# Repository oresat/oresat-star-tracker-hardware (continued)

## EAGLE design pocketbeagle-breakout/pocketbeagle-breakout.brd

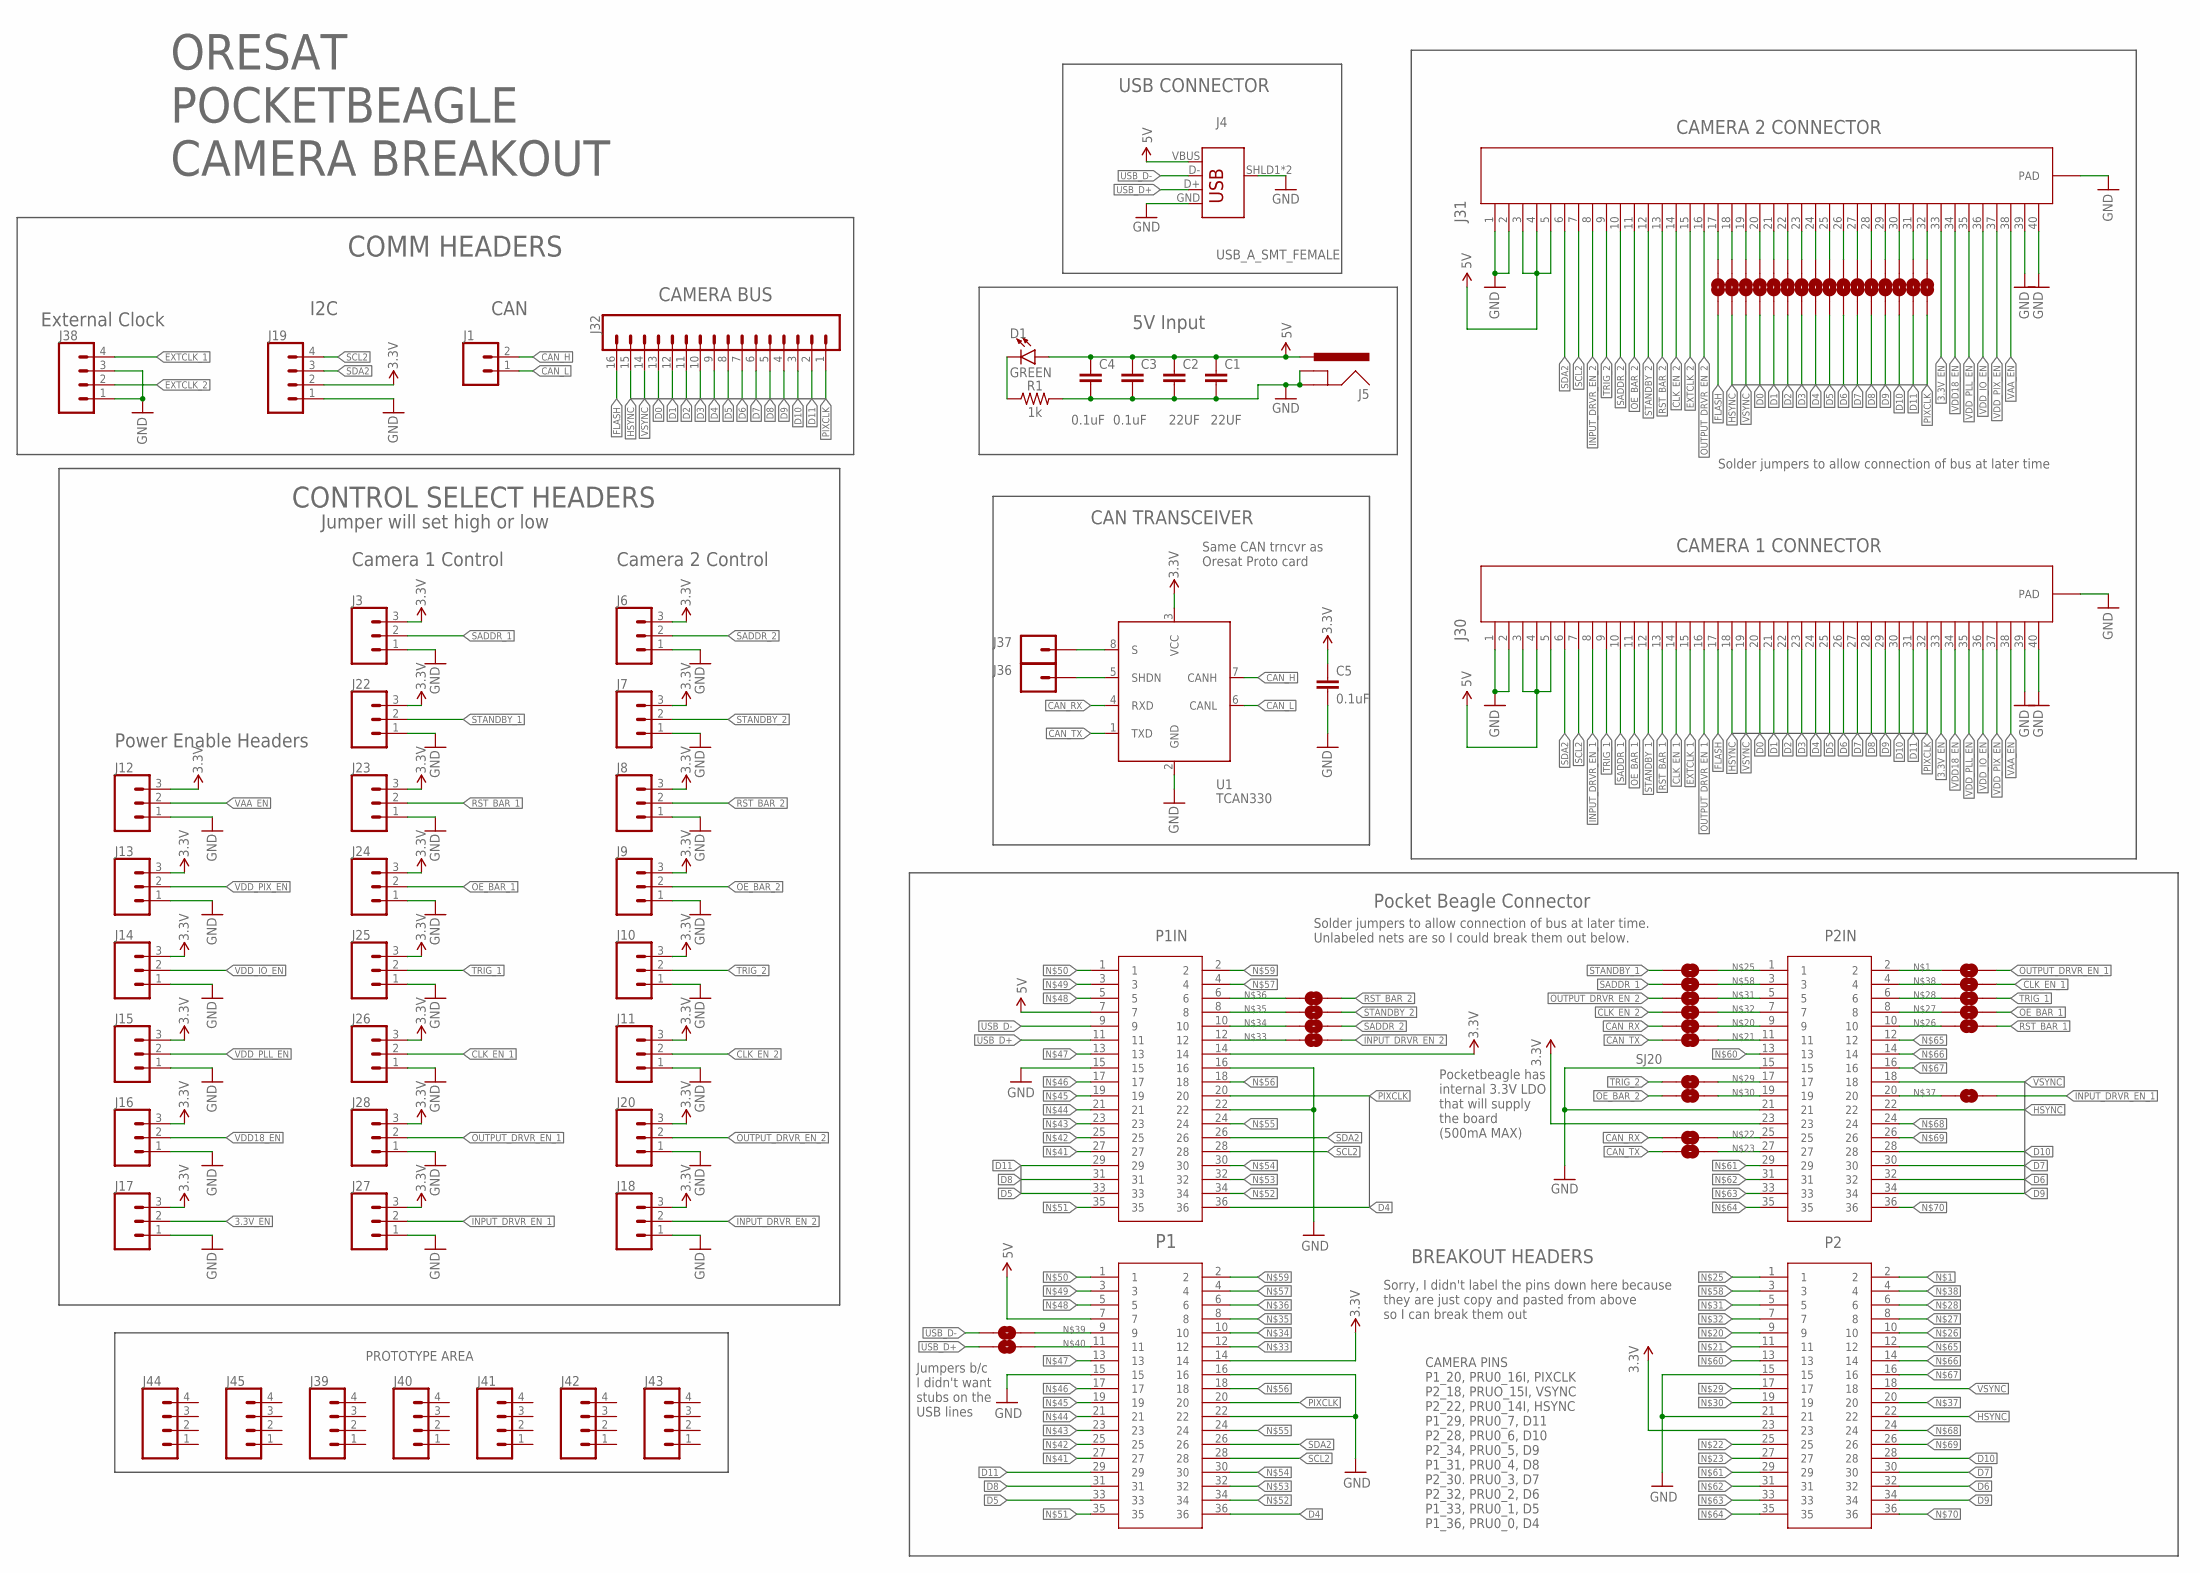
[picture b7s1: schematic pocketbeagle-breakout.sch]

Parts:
C1, C2: 22UF; 1210
C3, C4, C5: 0.1uF; 0603
D1: GREEN; LED-0603
J1: CONN_025MM; SCREWTERMINAL-5MM-2
J3, J6, J7, J8, J9, J10, J11, J12, J13, J14, J15, J16, J17, J18, J20, J22, J23, J24, J25, J26, J27, J28: CONN_031X03_NO_SILK; 1X03_NO_SILK
J4: USB_A_SMT_FEMALE; USB-A-S-SILK-FEMALE
J5: POWER_JACK; POWER_JACK_PTH
J19, J38, J39, J40, J41, J42, J43, J44, J45: CONN_041X04_NO_SILK; 1X04_NO_SILK
J30, J31: 4-1734592-04-1734592-0; TE_4-1734592-0
J32: CONN_161X16_NO_SILK; 1X16_NO_SILK
J36, J37: CONN_01PTH_NO_SILK_YES_STOP; 1X01_NO_SILK
P1, P1IN, P2, P2IN: BCS-118-L-D-TE; CON36_2X18_TU_BCS
R1: 1k; 0603
SJ1, SJ2, SJ3, SJ4, SJ5, SJ6, SJ7, SJ8, SJ9, SJ10, SJ11, SJ12, SJ13, SJ14, SJ15, SJ16: SOLDERJUMPERNC2; SJ_2S-NOTRACE
SJ17, SJ18, SJ21, SJ22, SJ23, SJ24, SJ25, SJ26, SJ27, SJ28, SJ29, SJ30, SJ31, SJ32, SJ33, SJ34, SJ35, SJ36, SJ37, SJ38: SOLDERJUMPERNC; SJ_2S
SJ19, SJ20: SOLDERJUMPERTRACE; SJ_2S-TRACE
U1: TCAN330; SOT23-8_TI-DCN

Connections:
3.3V: C5.1, J3.3, J6.3, J7.3, J8.3, J9.3, J10.3, J11.3, J12.3, J13.3, J14.3, J15.3, J16.3, J17.3, J18.3, J19.2, J20.3, J22.3, J23.3, J24.3, J25.3, J26.3, J27.3, J28.3, P1.14, P1IN.14, P2.23, P2IN.23, U1.3 (VCC)
3.3V_EN: J17.2, J30.33, J31.33
5V: C1.1, C2.1, C3.1, C4.1, D1.A, J4.VBUS, J5.PWR, J30.3, J30.4, J30.5, J31.3, J31.4, J31.5, P1.7, P1IN.7
CAN_H: J1.2, U1.7 (CANH)
CAN_L: J1.1, U1.6 (CANL)
CAN_RX: SJ17.2, SJ19.2, U1.4 (RXD)
CAN_TX: SJ18.2, SJ20.2, U1.1 (TXD)
CLK_EN_1: J26.2, J30.14, SJ36.1
CLK_EN_2: J11.2, J31.14, SJ29.2
D0: J30.20, J32.13, SJ15.1
D1: J30.21, J32.12, SJ14.1
D2: J30.22, J32.11, SJ13.1
D3: J30.23, J32.10, SJ12.1
D4: J30.24, J32.9, P1.36, P1IN.36, SJ11.1
D5: J30.25, J32.8, P1.33, P1IN.33, SJ10.1
D6: J30.26, J32.7, P2.32, P2IN.32, SJ9.1
D7: J30.27, J32.6, P2.30, P2IN.30, SJ8.1
D8: J30.28, J32.5, P1.31, P1IN.31, SJ7.1
D9: J30.29, J32.4, P2.34, P2IN.34, SJ6.1
D10: J30.30, J32.3, P2.28, P2IN.28, SJ5.1
D11: J30.31, J32.2, P1.29, P1IN.29, SJ4.1
EXTCLK_1: J30.15, J38.4
EXTCLK_2: J31.15, J38.2
FLASH: J30.17, J32.16, SJ16.2
GND: C1.2, C2.2, C3.2, C4.2, C5.2, J3.1, J4.GND, J4.SHLD1 (SHIELD), J4.SHLD2 (SHIELD), J5.GND, J5.GNDBREAK, J6.1, J7.1, J8.1, J9.1, J10.1, J11.1, J12.1, J13.1, J14.1, J15.1, J16.1, J17.1, J18.1, J19.1, J20.1, J22.1, J23.1, J24.1, J25.1, J26.1, J27.1, J28.1, J30.1, J30.2, J30.39, J30.40, J30.S1 (PAD), J30.S2 (PAD), J31.1, J31.2, J31.39, J31.40, J31.S1 (PAD), J31.S2 (PAD), J38.1, J38.3, P1.15, P1.16, P1.22, P1IN.15, P1IN.16, P1IN.22, P2.15, P2.21, P2IN.15, P2IN.21, R1.2, U1.2 (GND)
HSYNC: J30.18, J32.15, P2.22, P2IN.22, SJ3.1
INPUT_DRVR_EN_1: J27.2, J30.8, SJ35.2
INPUT_DRVR_EN_2: J18.2, J31.8, SJ33.1
unnamed: P2.2, P2IN.2, SJ34.1
unnamed: J31.17, SJ16.1
unnamed: J31.18, SJ3.2
unnamed: J31.19, SJ2.2
unnamed: J31.20, SJ15.2
unnamed: J31.21, SJ14.2
unnamed: J31.22, SJ13.2
unnamed: J31.23, SJ12.2
unnamed: J31.24, SJ11.2
unnamed: J31.25, SJ10.2
unnamed: J31.26, SJ9.2
unnamed: J31.27, SJ8.2
unnamed: J31.28, SJ7.2
unnamed: J31.29, SJ6.2
unnamed: J31.30, SJ5.2
unnamed: J31.31, SJ4.2
unnamed: J31.32, SJ1.2
unnamed: J36.1, U1.5 (SHDN)
unnamed: J37.1, U1.8 (S)
unnamed: P2.9, P2IN.9, SJ19.1
unnamed: P2.11, P2IN.11, SJ20.1
unnamed: P2.25, P2IN.25, SJ17.1
unnamed: P2.27, P2IN.27, SJ18.1
unnamed: D1.C, R1.1
unnamed: P2.1, P2IN.1, SJ22.2
unnamed: P2.10, P2IN.10, SJ23.2
unnamed: P2.8, P2IN.8, SJ24.2
unnamed: P2.6, P2IN.6, SJ25.2
unnamed: P2.17, P2IN.17, SJ26.1
unnamed: P2.19, P2IN.19, SJ27.1
unnamed: P2.5, P2IN.5, SJ28.1
unnamed: P2.7, P2IN.7, SJ29.1
unnamed: P1.12, P1IN.12, SJ33.2
unnamed: P1.10, P1IN.10, SJ32.2
unnamed: P1.8, P1IN.8, SJ31.2
unnamed: P1.6, P1IN.6, SJ30.2
unnamed: P2.20, P2IN.20, SJ35.1
unnamed: P2.4, P2IN.4, SJ36.2
unnamed: P1.9, SJ37.1
unnamed: P1.11, SJ38.1
unnamed: P1.27, P1IN.27
unnamed: P1.25, P1IN.25
unnamed: P1.23, P1IN.23
unnamed: P1.21, P1IN.21
unnamed: P1.19, P1IN.19
unnamed: P1.17, P1IN.17
unnamed: P1.13, P1IN.13
unnamed: P1.5, P1IN.5
unnamed: P1.3, P1IN.3
unnamed: P1.1, P1IN.1
unnamed: P1.35, P1IN.35
unnamed: P1.34, P1IN.34
unnamed: P1.32, P1IN.32
unnamed: P1.30, P1IN.30
unnamed: P1.24, P1IN.24
unnamed: P1.18, P1IN.18
unnamed: P1.4, P1IN.4
unnamed: P2.3, P2IN.3, SJ21.2
unnamed: P1.2, P1IN.2
unnamed: P2.13, P2IN.13
unnamed: P2.29, P2IN.29
unnamed: P2.31, P2IN.31
unnamed: P2.33, P2IN.33
unnamed: P2.35, P2IN.35
unnamed: P2.12, P2IN.12
unnamed: P2.14, P2IN.14
unnamed: P2.16, P2IN.16
unnamed: P2.24, P2IN.24
unnamed: P2.26, P2IN.26
unnamed: P2.36, P2IN.36
OE_BAR_1: J24.2, J30.11, SJ24.1
OE_BAR_2: J9.2, J31.11, SJ27.2
OUTPUT_DRVR_EN_1: J28.2, J30.16, SJ34.2
OUTPUT_DRVR_EN_2: J20.2, J31.16, SJ28.2
PIXCLK: J30.32, J32.1, P1.20, P1IN.20, SJ1.1
RST_BAR_1: J23.2, J30.13, SJ23.1
RST_BAR_2: J8.2, J31.13, SJ30.1
SADDR_1: J3.2, J30.10, SJ21.1
SADDR_2: J6.2, J31.10, SJ32.1
SCL2: J19.4, J30.7, J31.7, P1.28, P1IN.28
SDA2: J19.3, J30.6, J31.6, P1.26, P1IN.26
STANDBY_1: J22.2, J30.12, SJ22.1
STANDBY_2: J7.2, J31.12, SJ31.1
TRIG_1: J25.2, J30.9, SJ25.1
TRIG_2: J10.2, J31.9, SJ26.2
USB_D+: J4.D+, P1IN.11, SJ38.2
USB_D-: J4.D-, P1IN.9, SJ37.2
VAA_EN: J12.2, J30.38, J31.38
VDD18_EN: J16.2, J30.34, J31.34
VDD_IO_EN: J14.2, J30.36, J31.36
VDD_PIX_EN: J13.2, J30.37, J31.37
VDD_PLL_EN: J15.2, J30.35, J31.35
VSYNC: J30.19, J32.14, P2.18, P2IN.18, SJ2.1

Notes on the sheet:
I2C
Camera 2 Control
CAMERA PINS P1_20, PRU0_16I, PIXCLK P2_18, PRUO_15I, VSYNC P2_22, PRU0_14I, HSYNC P1_29, PRU0_7, D11 P2_28, PRU0_6, D10 P2_34, PRU0_5, D9 P1_31, PRU0_4, D8 P2_30. PRU0_3, D7 P2_32, PRU0_2, D6 P1_33, PRU0_1, D5 P1_36, PRU0_0, D4
Power Enable Headers
Camera 1 Control
Pocket Beagle Connector
CAN
PROTOTYPE AREA
CAN TRANSCEIVER
External Clock
USB CONNECTOR
5V Input
ORESAT POCKETBEAGLE CAMERA BREAKOUT
BREAKOUT HEADERS
CAMERA BUS
CAMERA 2 CONNECTOR
CAMERA 1 CONNECTOR
Solder jumpers to allow connection of bus at later time
CONTROL SELECT HEADERS
Jumper will set high or low
COMM HEADERS
Solder jumpers to allow connection of bus at later time. Unlabeled nets are so I could break them out below.
Sorry, I didn't label the pins down here because they are just copy and pasted from above so I can break them out
Jumpers b/c I didn't want stubs on the USB lines
Same CAN trncvr as Oresat Proto card
Pocketbeagle has internal 3.3V LDO that will supply the board (500mA MAX)

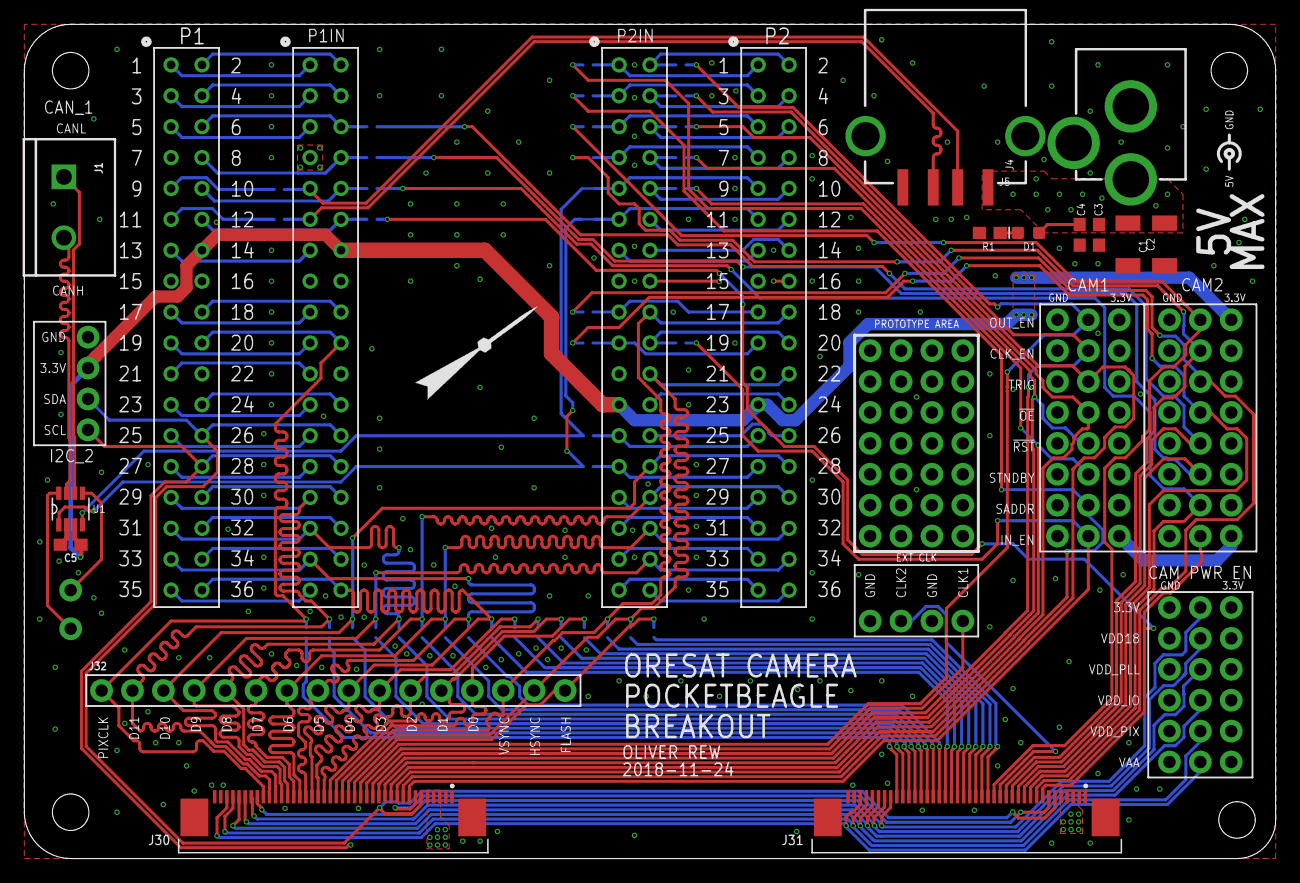
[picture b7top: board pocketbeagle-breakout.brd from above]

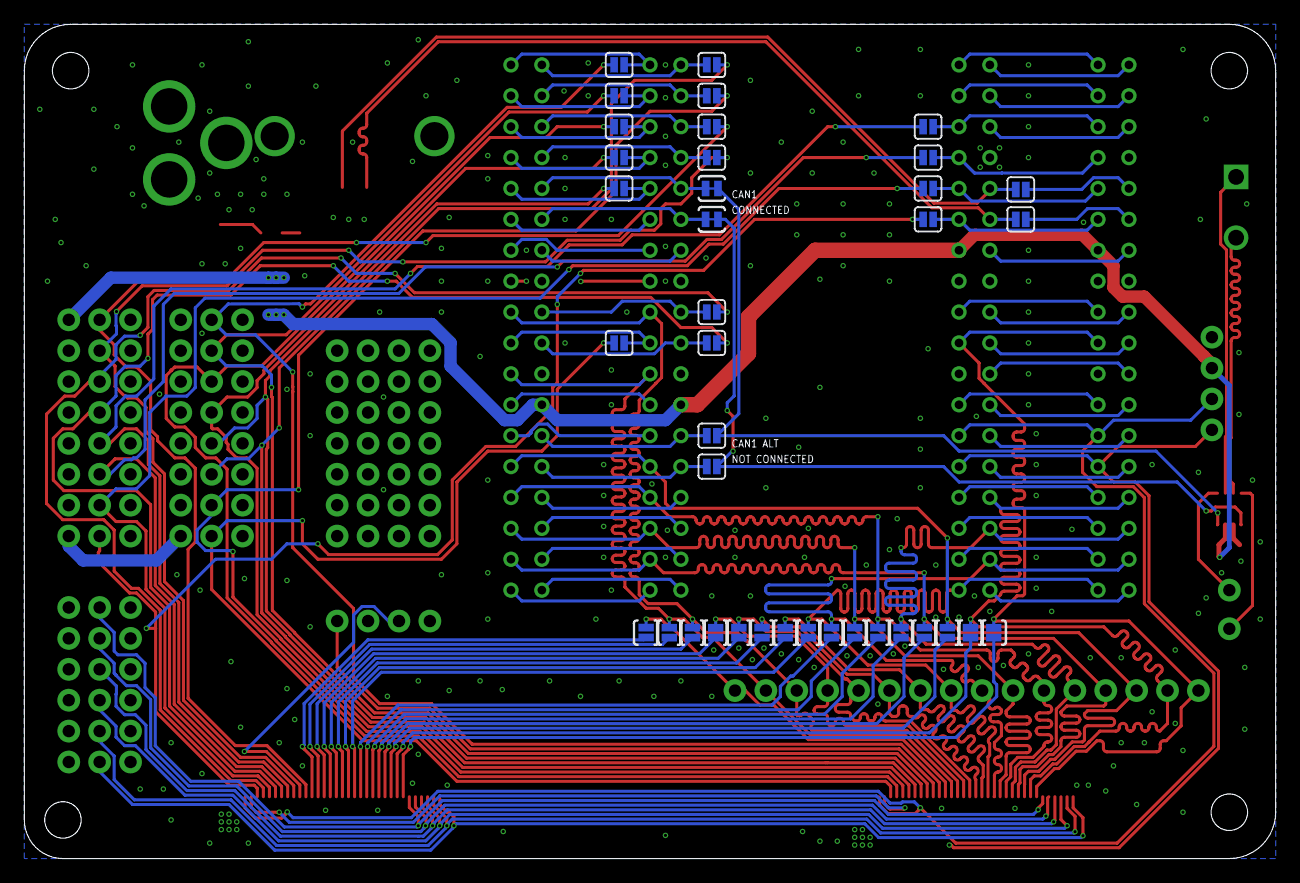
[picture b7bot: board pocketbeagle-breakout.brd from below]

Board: 4 copper layers, 102.9 x 68.6 mm, 91 parts (39 on the bottom side), 121 nets.

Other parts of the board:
U$1: PSAS_LOGO_10X10_NEW
U$2: POLARITY_SYMBOL_SMALL

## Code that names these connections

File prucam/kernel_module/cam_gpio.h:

#include <linux/module.h> // needed for LKM macros and such
#include <linux/kernel.h>         // Contains types, macros, functions for the kernel
#include <linux/gpio.h>   
#include <linux/delay.h>

// Module license, without this many funcs can't be used
MODULE_LICENSE("GPL");

// Camera Control Pin Numbers
#define GPIO_FLASH 16
#define GPIO_BUS_OE 97
#define GPIO_CAM_OE 96
#define GPIO_CLK_EN 106
#define GPIO_INPUT_EN 85
#define GPIO_RESET 84
#define GPIO_SADDR 83
#define GPIO_STANDBY 82
#define GPIO_TRIGGER 98
#define GPIO_VREG_EN 100

int init_cam_gpio(void);
void camera_enable(void); 
int free_cam_gpio(void);

typedef struct {
  uint8_t num;
  bool init;
  bool enable; 
  char* label;
} gpio;

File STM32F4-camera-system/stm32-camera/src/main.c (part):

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
    //init GPIO for debug LEDs
    GPIOinit();
    GPIO_SetBits(GPIOD, GPIO_Pin_13); //Orange LED is status, ON = STANDBY, OFF = BUSY
    GPIO_SetBits(GPIOD, GPIO_Pin_14);

    //GPIO_SetBits(GPIOD, GPIO_Pin_6); //pull this low to enable the camera
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								  | GPIO_Pin_4 | GPIO_Pin_5 | GPIO_Pin_6;
	GPIO_Init(GPIOE, &GPIO_InitStructure);

	/* D5(PB6), VSYNC(PB7) */
	GPIO_InitStructure.GPIO_Pin = GPIO_Pin_6 | GPIO_Pin_7;
	GPIO_Init(GPIOB, &GPIO_InitStructure);

	/* PCLK(PA6) HSYNC(PA4)*/
	GPIO_InitStructure.GPIO_Pin = GPIO_Pin_4 | GPIO_Pin_6;
	GPIO_InitStructure.GPIO_Mode = GPIO_Mode_AF;
	GPIO_InitStructure.GPIO_OType = GPIO_OType_PP;
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
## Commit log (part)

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2017-11-08 yay official oresat repo!
2018-01-05 deleted old useless files
2018-01-06 readme changes
2018-01-06 tried unsuccesfully to split apart the main code
2018-01-19 Started writing a decoder for binary star catalogue
2018-01-19 added write functionality to binary decoder.
2018-01-20 Create ST_Optimization_Flow_Notes
    Put down some preliminary notes for ST optimization
2018-01-20 Update ST_Optimization_Flow_Notes
2018-01-22 added some folders
2018-02-17 added code
2018-02-17 housekeeping
2018-02-17 cleaning
2018-02-17 mawr
2018-02-17 fdsfs
2018-02-17 consolidation
2018-02-17 fdsffs
2018-02-17 elf path
2018-02-17 more success
2018-02-20 Got the camera working again. Had to move extern variable to main.h
2018-02-20 Removed unused functions and added Orange Standby LED
2018-02-24 UART Image tranfer is working well. Started playing with SCCB Registers.
2018-03-14 Double Buffering is in its infancy but working!
2018-03-15 Double Buffer is working and image is being reconstructed from lines.
2018-03-27 Added AR0130-dev-board I have been working on.
2018-04-02 updated BRD file
2018-04-03 more updates to schematic
2018-04-05 started rerouted board
2018-04-06 made breakout board for Camera Module
2018-04-06 finishing touches!
2018-04-06 Ready for design review
2018-04-07 Initial commit with script for camera testing.
2018-04-11 cleaned up some routing, added some test points
2018-04-19 developing the camera control program
2018-04-20 blah blah
2018-04-27 i dont know what changed, deal with it
2018-04-28 more final touches on bouard
2018-04-30 Please don't add temporary files!
2018-05-11 copied working serial camera program
2018-05-11 Added gain control to image test.
2018-05-19 edited executability
2018-05-19 up and running on the BeagleBone
2018-05-29 EVERYTHING IS FINE. Final touches on board that noone can even remember why we are redesigning in the first place?
2018-06-21 Rewrote startracker.py for readability.
2018-06-21 Rewrote calibrate.py for readability.
2018-06-21 Removed ESA testing and regeneration. (this will be useless in space)
2018-06-22 Remove UBuffalo-unique science camera.
2018-06-25 Always clear old calibration data.
2018-06-25 Remove plot generation during calibration.
2018-06-26 Remove unnecessary imports for calibration.
2018-06-26 Discovered the joy of downsampling during calibration.
2018-06-26 Remove pickling artifact.
2018-07-01 Add images for preprocessor testing.
2018-07-01 Prepped sample photos
2018-07-03 Threshold the ideal image
2018-07-05 Image pre-processing based on black pixel analysis. Doesn't require 'ideal' image.
2018-07-06 Fine tune pixel cutoff values
2018-07-08 Created images to test blur detection
2018-07-08 Blur detection based on Laplacian operator
2018-07-09 Streamlining
2018-07-11 Better calibration performance through sigma noise reduction parameter
2018-07-21 adding some i2c related arduino sketches
2018-07-22 Added i2c writing sketch
2018-07-26 Complete rewrite of startracker.py
2018-07-26 Make sure everything still works on the BeagleBone
2018-07-27 Confirm the integration works on the BeagleBone
2018-08-10 FINALLY up and running again, but no idea why everything is slower
2018-08-10 Speeds are back to normal
2018-10-14 made repo with inital files
2018-10-14 woah, it sorta works
2018-10-14 added git ignore
2018-10-15 quick address fix
2018-10-20 got a very fast transfer working
2018-11-16 modified for pocketbeagle
2018-11-19 got double buffer transfer working. Refactored code to resemble image data
2018-11-21 successfully reading the image sensor test pattern at 14MHz
2018-11-22 bunch of old changes from my laptop, dont know entirely what's in here
2018-11-26 final touches on pocketbeagle breakout
2018-11-26 slightly moved connector
2018-11-26 slightly moved via
2018-11-26 address review comments: used round hole on USB and power, changed CAN connector, other small stuff
2018-11-26 arg temp files
2018-11-26 Fixed flow through on layer 15 because OCD.
2018-12-13 Actually working on the PocketBeagle
2018-12-14 integrated i2c image sensor programming
2018-12-15 minor stuff
2018-12-15 added some delays to writing the i2c registers, added a small delay to ARM side program to stop ARM code from hogging the flags in memory
2018-12-15 moved pru camera stuff to subdir
2018-12-16 made loop volatile, added delay, cleaned up message
2018-12-16 made some vars volatile. now using CMA base address, not sure if this is better? added compiler optimization flag, cleanup
2018-12-17 using memcpy successfully except for a weird spot missing data
2018-12-17 added kernel module code borrowed from derek malloy tutorial
2019-01-26 Sockets working independently of OpenStarTracker
2019-01-26 changed directory name
2019-02-01 Switched to UNIX socket
2019-02-03 have a basic kernel driver/PRU handshake working
2019-02-07 Everything transferred to socket except actual position info
2019-02-18 stuggling with registering a platform device
2019-03-01 still struggling to get an interrupt
2019-03-08 First pass of manual image transfer working
2019-03-13 Remove loops and delays
2019-04-08 got the pru intc firing, couldn't figure out the resource tables so just set the registers myself
2019-04-19 typo
2019-04-20 I think I am getting image data now
2019-04-21 pictures!
2019-04-21 did more cleanup
2019-04-21 readme prettying
2019-04-28 Improve socket communication and add file writing
2019-05-01 make it loop
2019-05-20 working with a smaller set of registers, but the picture doesn't look great
2019-05-24 Integrate FLIF into image transfer
2019-06-21 moved kmalloc to probe
2019-07-23 put my schematic onto the current proto card and arranged some things
2019-08-04 some final touchs, think it's ready for review
2019-08-04 removed another unnecessary file
2019-08-04 small aesthetic changes
2019-08-04 rerouted camera bus
2019-08-05 fixed XO footprint, filleted edges
2019-08-05 some small length matching
2019-08-05 moved some traces
2019-08-07 fixed some ERC errors
2019-08-07 moved some labels
2019-09-13 few more touches on schematic
2019-09-13 formatting
2019-09-17 started layout
2019-09-28 ooof, all test points routed, now need to revise usb circuit
2019-09-29 made USB breakout board, added OPD schematic
2019-09-30 ERC and DRC errors
2019-09-30 broke out some pins
2019-09-30 added more labels
2019-09-30 moar VIAS
2019-09-30 added silk on resistors
2019-09-30 moved chip a bit
2019-09-30 last minute changes
2019-10-03 added holes for lens mount
2019-10-13 added covariance calculations and new method for quaternion-based attitude estimation
2019-11-12 Reorganize directory
2019-11-13 Rewrite star tracker front-end in Python3 with D-Bus integration
2019-12-01 deleted TODOs
2019-12-30 Working Python 3.6 front end
2020-01-03 Write example client
2020-01-03 made a few minor adjustments when I was making the BOMs
2020-01-10 Add threading
2020-01-15 added some octavo board utils
2020-01-18 made some progress with gpio device tree
2020-01-19 got GPIO working for one camera gpio, now need to add the rest
2020-01-19 did some clean up on the image sensor registers
2020-01-19 added AR0130 ini file
2020-01-20 put gpio stuff in own file and changed Makefile to build it right
2020-01-23 removed pulldown from device tree gpio
2020-01-29 Extremely ugly daemon with broadcasting
2020-02-03 added check for kernel version in prucam
2020-02-12 make a new branch for the state machine
2020-02-17 Initial flatsat run
2020-02-19 Add dbus config files to repo
2020-02-22 Migrated software to separate repo
2020-05-08 update camera-card notes
2020-05-25 refactored the camera circuit section
2020-05-26 cleaned up labels and sysboot pins
2020-05-26 extended 3.3v power plane
2020-05-26 minor changes to power plane
2020-05-31 implemented design review changes. Cleaned up the repo a bit. Added generic SPI EEPROM footprint for booting
2020-07-08 added digikey BOMs for star tracker card and camera board
2020-07-24 added DPN for connector
2020-07-25 move pru kernel module / firmware to new repo
2020-07-29 updated star tracker board picture
2020-08-16 typos in eMMC guide
2020-08-24 added AR0134 init file. minor comment change
2020-10-23 updated board and BOM with rev1.1 notes
2020-10-24 added DXF for new camera card
2020-10-24 added new outline DXF and updated board
2020-10-26 chore: a couple updates from design review
    - add DXF layer for board outline footprint
    - remove copper restrict from under camera mounts
    - move FFC x-0.4mm to align with camera board(was off previously)
    - add parts for I2C0 ESD circuit to BOM
2020-10-30 updated BOM with extra caps
2020-11-23 Updated card outline (still v1.3) to add extraction hole, no other changes.
2020-12-08 V1.2 off to fab! Tweaks on silkscreen, including flight hardware indiciator.
2020-12-24 feat: created a camera board breakout and pmod adapter
2021-01-16 chore: add BOM warning file, will fix later
2021-02-19 backup
2021-06-14 chore: update photo
2025-07-06 Saner directory name
2025-07-06 Import EAGLE v1.2 into KiCAD 9.0.2
2025-07-06 Fixed some ERCs and imported schematic into layout
2026-01-30 More EAGLE import clean up
    Fixed BOM, still needs 0402 passives. Fixed ERCs, and a bunch of DRCs. U1 still needs footprint cleanup.
2026-01-30 More EAGLE import cleanup
    Fixed sheets, did some ERC cleanup, imported into layout, impmorted 4 layer DRC rules.
2026-01-31 Updated BOM for daughterboard
2026-02-05 Schematic Overhaul of v1.3
    Changed schematic to hierarchical, changed debug connector, updated OPD, removed JTAG, and ESD protection on removed connectors
2026-03-13 initial commit for action
2026-04-01 Minor update to j4
2026-04-03 Updated Octavo schematic
    Removed many testpoints, added filter to 1.8v reference, tied some signals to ground with pull down resistor, added NCs to multiple pins.
2026-04-04 Update
    Update to the octavo schematic
2026-04-06 No ERCs now
2026-04-11 Routine push
2026-04-15 Big almost-done cleanup
    Fixed a bunch of things in the schematic. Compared against C3 Octavo. Fixed all weird ERCs. Cleaned up a lot of planes on the layout. Moved uart switch, rerouted a bunch of traces for better layout. 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
2026-04-20 BOM 99% completed, push for final review
2026-05-04 Star Tracker v1.3 files, including new Makefile, Readme, and fixes in ERC, DRC, and layout
2026-05-07 Added IMU
    added IMU, and i2c pull up resistors to schematic.
2026-05-10 star tracker camera board 2.0
2026-05-19 2.0 routine push
2026-05-21 No significant change; upgraded to KiCad 10.0.3, minor aesthetic tweaks to schematic
2026-05-23 Cleaned up files
2026-05-26 Update on camera board
    Finished layout and routing. Only needs DRC error fixing and silk screen placement
2026-06-04 Routine Push
    Updated schematic and layout. about 60% done with routing.
2026-06-05 Star Tracker 2.0
    Layout and routing 100% completed. Only needs minor adjustments for silkscreen and camera mounting holes.
2026-06-05 Update
    Changed camera mount drill holes to be incremented by 5 mm. Made minor changes to test point locations on data lines.
2026-06-07 Final Cleanup
    Added 3d models to camera and star tracker module. Tightened routing and changed power planes as per DR from Friday.
2026-06-15 Bom update
    Updated BOM to correct connector MPN and other misc components
2026-06-19 Minor PCB changes
    updated description of component in BOM, changed filet radius on polygon pours, changed PCB footprint to Star tracker 2.0 PCB. Added more ground vias.
2026-06-19 Update to Camera Board
    Update BOM for camera board, replaced lower tier dielectric caps to X7R
2026-06-20 Minor Alterations
    small change to PCB and silkscreen placement/component routing.
2026-06-21 Added pull up and pull down resistors
    aded PU and PD resistors for firmware revision set.
2026-06-22 Added extra Testpoints
